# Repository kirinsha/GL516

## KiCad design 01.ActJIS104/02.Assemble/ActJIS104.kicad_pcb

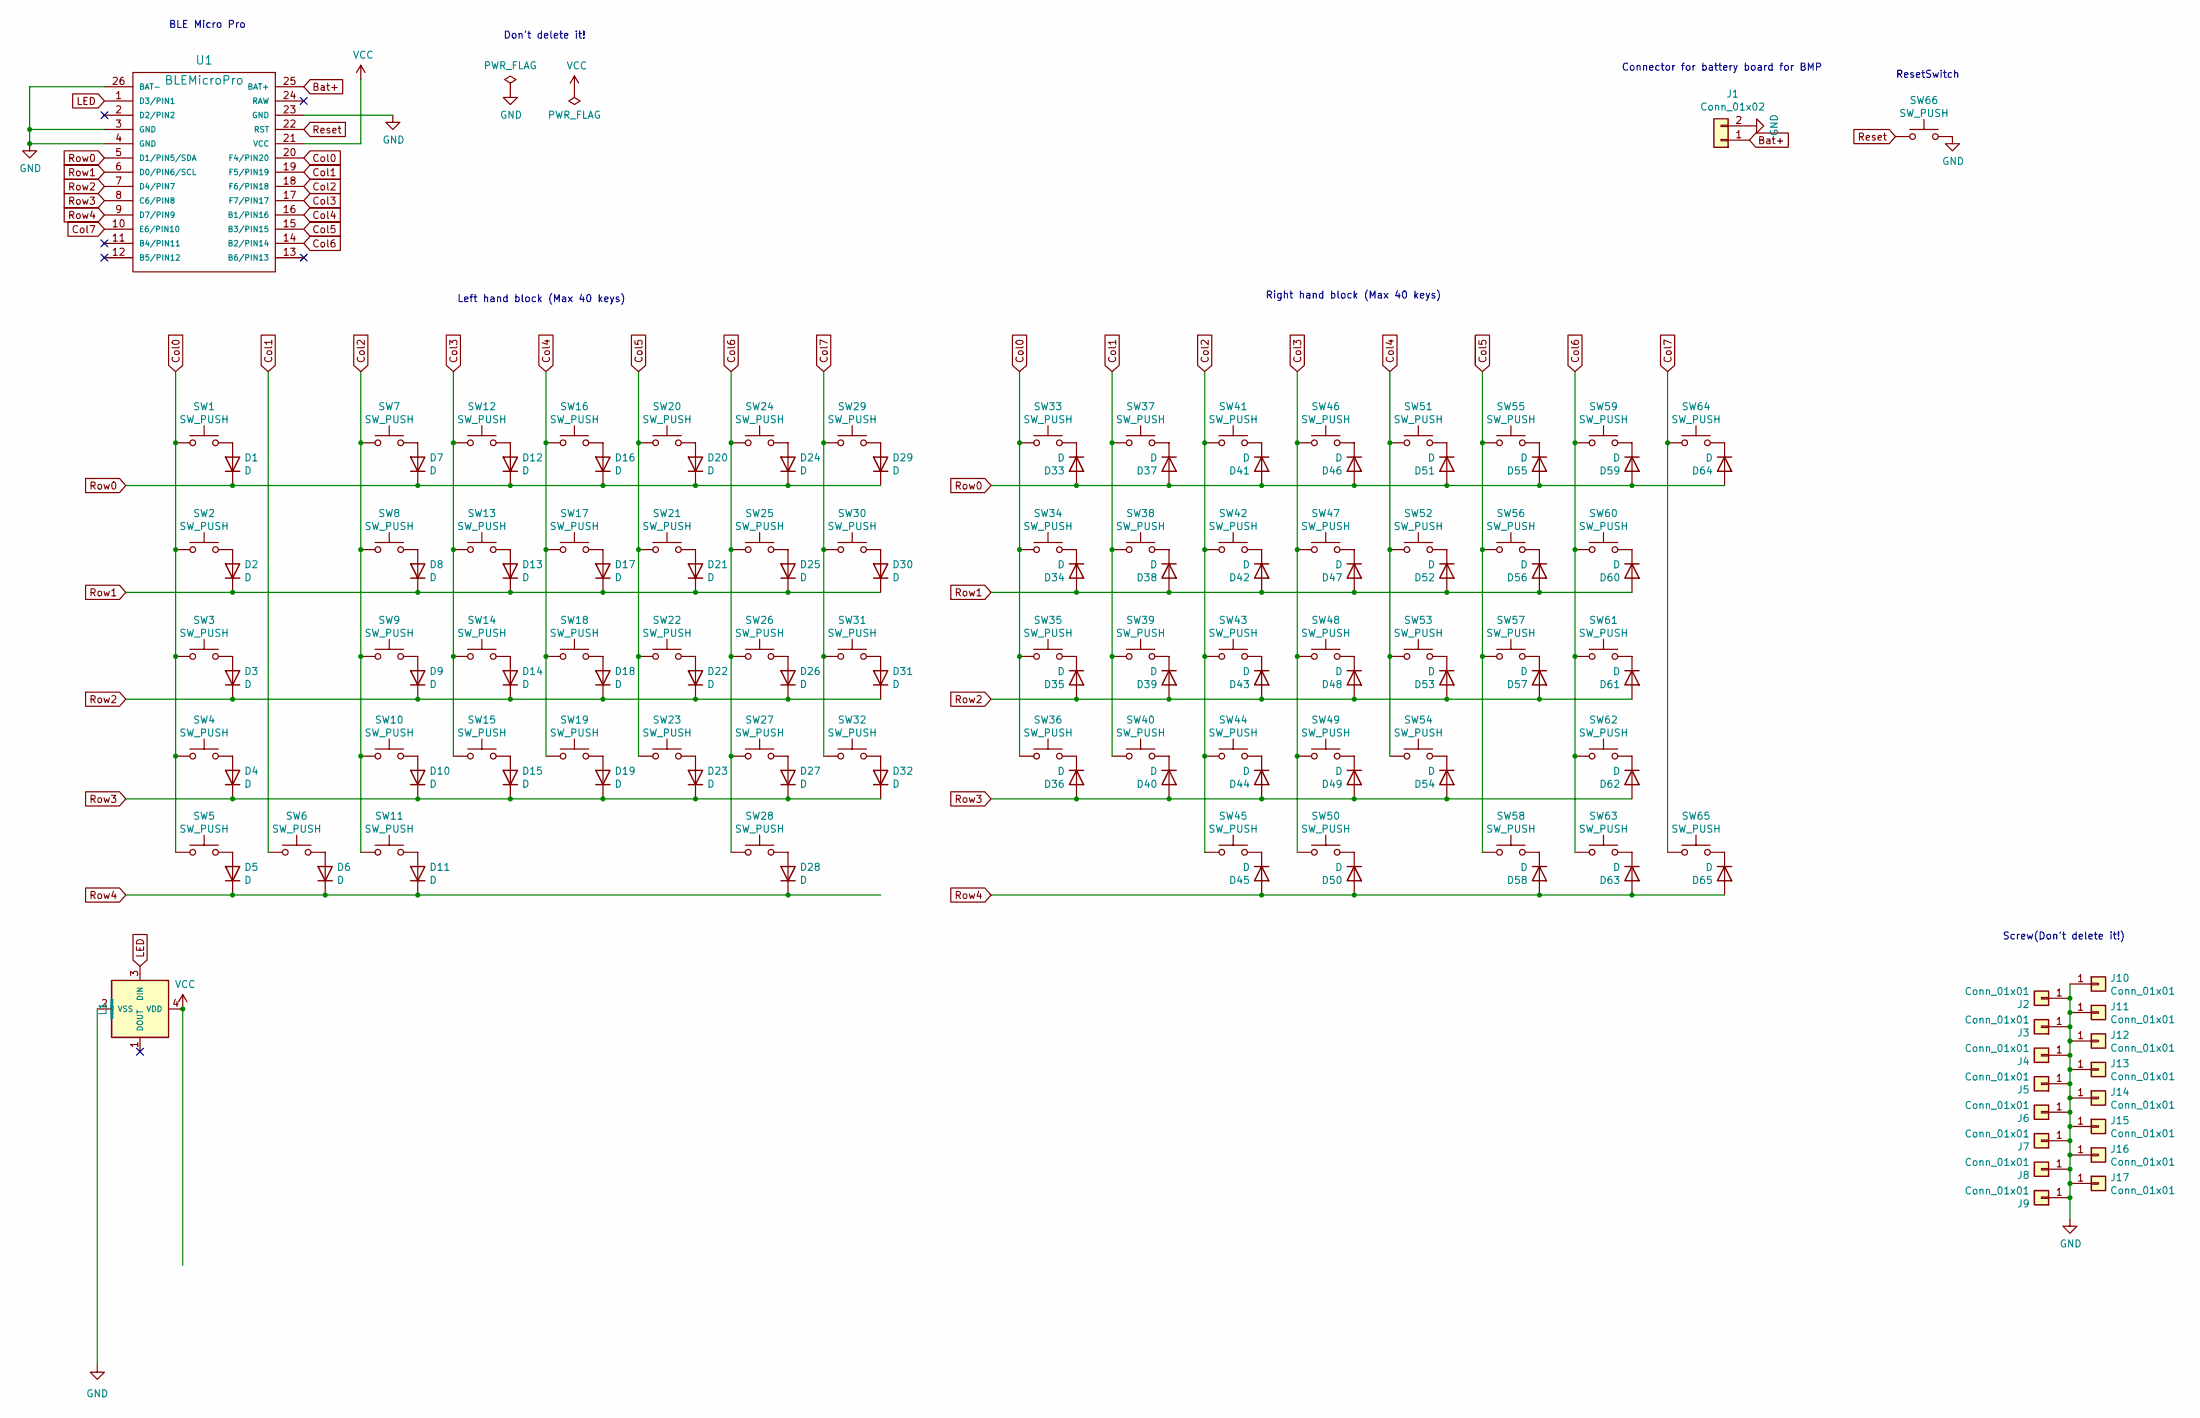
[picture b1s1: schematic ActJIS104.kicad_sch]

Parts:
D1, D2, D3, D4, D5, D6, D7, D8, D9, D10, D11, D12, D13, D14, D15, D16, D17, D18, D19, D20, D21, D22, D23, D24, D25, D26, D27, D28, D29, D30, D31, D32, D33, D34, D35, D36, D37, D38, D39, D40, D41, D42, D43, D44, D45, D46, D47, D48, D49, D50, D51, D52, D53, D54, D55, D56, D57, D58, D59, D60, D61, D62, D63, D64, D65: D; Diode_TH_SMD
J1: Conn_01x02; Battery_XH2.5_GL_PCB
J2, J3, J4, J5, J6, J7: Conn_01x01; m2_Screw_Hole_EdgeCuts
J8, J9, J10, J11, J12, J13, J14, J15, J16, J17: Conn_01x01; m2_Screw_Hole_Fab
L1: SK6812MINI; LED_SK6812MINI-E_BL
SW1, SW7, SW8, SW9, SW10, SW12, SW13, SW14, SW15, SW16, SW17, SW18, SW19, SW20, SW21, SW22, SW23, SW24, SW25, SW26, SW27, SW29, SW30, SW31, SW32, SW33, SW34, SW35, SW36, SW37, SW38, SW39, SW40, SW41, SW42, SW43, SW44, SW46, SW47, SW48, SW49, SW51, SW52, SW53, SW54, SW55, SW56, SW57, SW59, SW63, SW65: SW_PUSH; CherryMX_Hotswap_1u
SW2, SW60: SW_PUSH; CherryMX_Hotswap_1.5u
SW3: SW_PUSH; CherryMX_Hotswap_1.75u
SW4, SW61: SW_PUSH; CherryMX_Hotswap_2.25u
SW5, SW6, SW11, SW45, SW50, SW58: SW_PUSH; CherryMX_Hotswap_1.25u
SW28: SW_PUSH; CherryMX_Hotswap_6.25u
SW62: SW_PUSH; CherryMX_Hotswap_2.75u
SW64: SW_PUSH; CherryMX_Hotswap_2u
SW66: SW_PUSH; ResetSW
U1: BLEMicroPro; Micon_BMP_GL

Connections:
Bat+: J1.1, U1.25 (BAT+)
Col0: SW1.1, SW2.1, SW3.1, SW4.1, SW5.1, SW33.1, SW34.1, SW35.1, SW36.1, U1.20 (F4/PIN20)
Col1: SW6.1, SW37.1, SW38.1, SW39.1, SW40.1, U1.19 (F5/PIN19)
Col2: SW7.1, SW8.1, SW9.1, SW10.1, SW11.1, SW41.1, SW42.1, SW43.1, SW44.1, SW45.1, U1.18 (F6/PIN18)
Col3: SW12.1, SW13.1, SW14.1, SW15.1, SW46.1, SW47.1, SW48.1, SW49.1, SW50.1, U1.17 (F7/PIN17)
Col4: SW16.1, SW17.1, SW18.1, SW19.1, SW51.1, SW52.1, SW53.1, SW54.1, U1.16 (B1/PIN16)
Col5: SW20.1, SW21.1, SW22.1, SW23.1, SW55.1, SW56.1, SW57.1, SW58.1, U1.15 (B3/PIN15)
Col6: SW24.1, SW25.1, SW26.1, SW27.1, SW28.1, SW59.1, SW60.1, SW61.1, SW62.1, SW63.1, U1.14 (B2/PIN14)
Col7: SW29.1, SW30.1, SW31.1, SW32.1, SW64.1, SW65.1, U1.10 (E6/PIN10)
GND: J1.2, J2.1, J3.1, J4.1, J5.1, J6.1, J7.1, J8.1, J9.1, J10.1, J11.1, J12.1, J13.1, J14.1, J15.1, J16.1, J17.1, L1.2 (VSS), SW66.2, U1.3 (GND), U1.4 (GND), U1.23 (GND), U1.26 (BAT-)
LED: L1.3 (DIN), U1.1 (D3/PIN1)
unnamed: D1.2 (A), SW1.2
unnamed: D2.2 (A), SW2.2
unnamed: D3.2 (A), SW3.2
unnamed: D4.2 (A), SW4.2
unnamed: D5.2 (A), SW5.2
unnamed: D6.2 (A), SW6.2
unnamed: D7.2 (A), SW7.2
unnamed: D8.2 (A), SW8.2
unnamed: D9.2 (A), SW9.2
unnamed: D10.2 (A), SW10.2
unnamed: D11.2 (A), SW11.2
unnamed: D12.2 (A), SW12.2
unnamed: D13.2 (A), SW13.2
unnamed: D14.2 (A), SW14.2
unnamed: D15.2 (A), SW15.2
unnamed: D16.2 (A), SW16.2
unnamed: D17.2 (A), SW17.2
unnamed: D18.2 (A), SW18.2
unnamed: D19.2 (A), SW19.2
unnamed: D20.2 (A), SW20.2
unnamed: D21.2 (A), SW21.2
unnamed: D22.2 (A), SW22.2
unnamed: D23.2 (A), SW23.2
unnamed: D24.2 (A), SW24.2
unnamed: D25.2 (A), SW25.2
unnamed: D26.2 (A), SW26.2
unnamed: D27.2 (A), SW27.2
unnamed: D28.2 (A), SW28.2
unnamed: D29.2 (A), SW29.2
unnamed: D30.2 (A), SW30.2
unnamed: D31.2 (A), SW31.2
unnamed: D32.2 (A), SW32.2
unnamed: D33.1 (K), SW33.2
unnamed: D34.1 (K), SW34.2
unnamed: D35.1 (K), SW35.2
unnamed: D36.1 (K), SW36.2
unnamed: D37.1 (K), SW37.2
unnamed: D38.1 (K), SW38.2
unnamed: D39.1 (K), SW39.2
unnamed: D40.1 (K), SW40.2
unnamed: D41.1 (K), SW41.2
unnamed: D42.1 (K), SW42.2
unnamed: D43.1 (K), SW43.2
unnamed: D44.1 (K), SW44.2
unnamed: D45.1 (K), SW45.2
unnamed: D46.1 (K), SW46.2
unnamed: D47.1 (K), SW47.2
unnamed: D48.1 (K), SW48.2
unnamed: D49.1 (K), SW49.2
unnamed: D50.1 (K), SW50.2
unnamed: D51.1 (K), SW51.2
unnamed: D52.1 (K), SW52.2
unnamed: D53.1 (K), SW53.2
unnamed: D54.1 (K), SW54.2
unnamed: D55.1 (K), SW55.2
unnamed: D56.1 (K), SW56.2
unnamed: D57.1 (K), SW57.2
unnamed: D58.1 (K), SW58.2
unnamed: D59.1 (K), SW59.2
unnamed: D60.1 (K), SW60.2
unnamed: D61.1 (K), SW61.2
unnamed: D62.1 (K), SW62.2
unnamed: D63.1 (K), SW63.2
unnamed: D64.1 (K), SW64.2
unnamed: D65.1 (K), SW65.2
Reset: SW66.1, U1.22 (RST)
Row0: D1.1 (K), D7.1 (K), D12.1 (K), D16.1 (K), D20.1 (K), D24.1 (K), D29.1 (K), D33.2 (A), D37.2 (A), D41.2 (A), D46.2 (A), D51.2 (A), D55.2 (A), D59.2 (A), D64.2 (A), U1.5 (D1/PIN5/SDA)
Row1: D2.1 (K), D8.1 (K), D13.1 (K), D17.1 (K), D21.1 (K), D25.1 (K), D30.1 (K), D34.2 (A), D38.2 (A), D42.2 (A), D47.2 (A), D52.2 (A), D56.2 (A), D60.2 (A), U1.6 (D0/PIN6/SCL)
Row2: D3.1 (K), D9.1 (K), D14.1 (K), D18.1 (K), D22.1 (K), D26.1 (K), D31.1 (K), D35.2 (A), D39.2 (A), D43.2 (A), D48.2 (A), D53.2 (A), D57.2 (A), D61.2 (A), U1.7 (D4/PIN7)
Row3: D4.1 (K), D10.1 (K), D15.1 (K), D19.1 (K), D23.1 (K), D27.1 (K), D32.1 (K), D36.2 (A), D40.2 (A), D44.2 (A), D49.2 (A), D54.2 (A), D62.2 (A), U1.8 (C6/PIN8)
Row4: D5.1 (K), D6.1 (K), D11.1 (K), D28.1 (K), D45.2 (A), D50.2 (A), D58.2 (A), D63.2 (A), D65.2 (A), U1.9 (D7/PIN9)
VCC: L1.4 (VDD), U1.21 (VCC)

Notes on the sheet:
Left hand block (Max 40 keys)
Connector for battery board for BMP
BLE Micro Pro
ResetSwitch
Screw(Don't delete it!)
Don't delete it!
Right hand block (Max 40 keys)

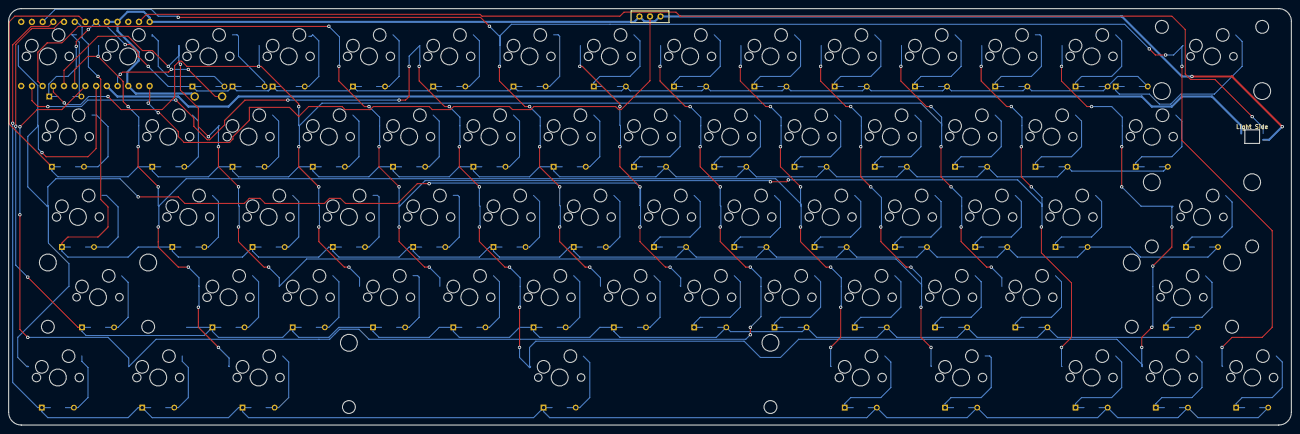
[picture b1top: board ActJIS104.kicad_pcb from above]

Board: 2 copper layers, 304.3 x 98.8 mm, 136 parts (0 on the bottom side), 83 nets.

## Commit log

2022-10-15 Create LICENCE
2022-10-15 Update LICENCE
